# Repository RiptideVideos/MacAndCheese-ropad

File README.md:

# MacAndCheese-ropad

The MacAndCheese-ropad is a 4x4 macropad running on a Xiao RP2040. All 16 of the macropad buttons are fully customizable with the QMK firmware or other firmware that the RP2040 supports. 

The MacAndCheese-ropad is intended to be used for daily tasks like copying, pasting, taking a screenshot, ect. THe buttons can also be used as extra function buttons (up to 8 on MacOS and 12 on Windows). Using more adanced software, the buttons could be tied to app specific functions or really anything that can be run on a computer.

> Learn more about button use for QMK here: https://docs.qmk.fm/keycodes_basic

I built the MacAndCheese-ropad because I thought it would be a fun but not to hard challage, it has been just as expected. While some of it was smooth sailing a lot was feeling like I was in the dark on many things, however I was able to pull through and continue the project. I hope this macropad makes me more productive and proud to have somthing I worked hard on be usful to me.

## The Design:

The design features 16 square keys layed out in a 4x4 grid.
- The keys are Cherry MX switches.
- There is a empty space right of the keys which holds the Xiao RP2040.

> Onshape File: https://cad.onshape.com/documents/c366476147c6a16a111f20a0/w/74e1df7ada6eec6626497acf/e/e85a476c3b104135c352d93f?renderMode=0&uiState=69c80dd1942be0583aa661a2

## The PCB:

The PCB uses a matrix to support all 16 keys, a photo of the PCB in KiCad is below:

## The Firmware

The MacAndCheese-ropad uses the QMK firmware to give the keys uses, currentally the firmware is set up with 2 layers of keys. (The exact set up is in the repo).

## Bill of Materials

| Item | Qty | Source | Price | Unit Price | Provided by Hackpad? |
|------|-----|--------|-------|------------|----------------------|
| Seeed XIAO RP2040 | 1 | https://www.seeedstudio.com/XIAO-RP2040-v1-0-p-5026.html | $3.99 | $3.99 | Yes |
| 1N4148 Diodes | 16 | https://www.amazon.com/dp/B06XB1R2NK | ~$0.05	| $4.99 | Yes |
| Cherry MX Switches | 16 | https://www.amazon.com/Cherry-Switch-Mechanical-Keyboard-Switches/ | $0.55	| $19.99 | Yes |
| DSA Keycaps | 16 | https://www.amazon.com/Mechkeeb-Profile-Switches-Keyboard-Replacement/dp/B0BWDQ3NKK | ~$0.37 | $8.99 | Yes |
| PCB | 1 | JLC PCB | $4-7 | $4-7 | Via Grant |
| Soldering Iron | 1 | https://pine64.com/product/pinecil-smart-mini-portable-soldering-iron/ | $25.99 | $25.99 | Via Grant |

> Notes on BOM:
> The PCB price changes based on color, settings and deliver option.
> The exact Soldering Iron isn't needed for this project and you could get others online.

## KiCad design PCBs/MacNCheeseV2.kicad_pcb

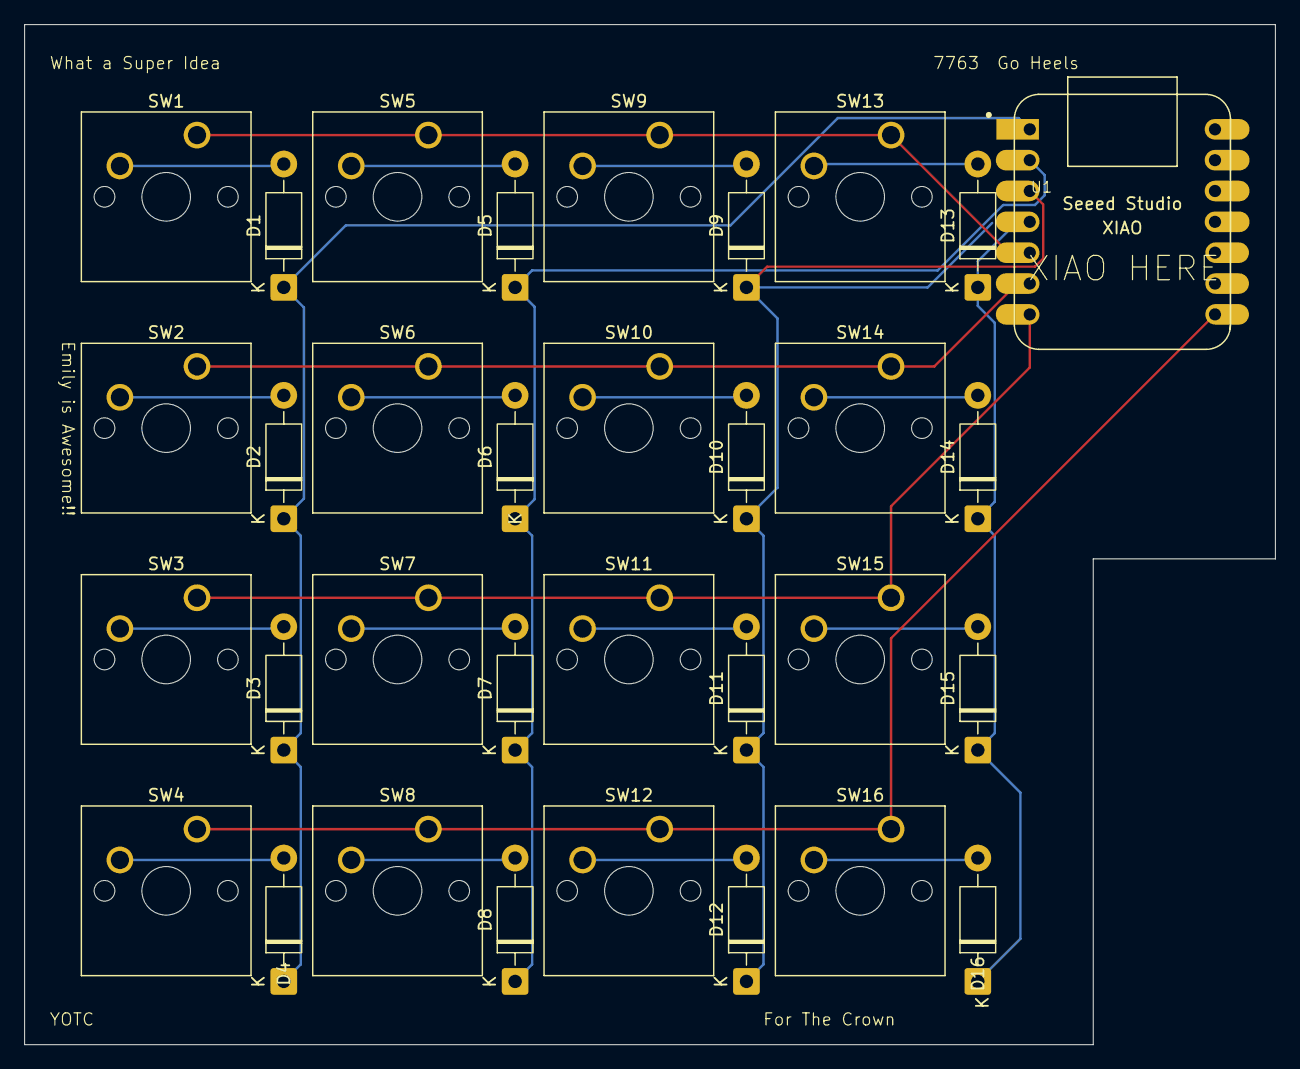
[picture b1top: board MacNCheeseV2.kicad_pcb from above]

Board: 2 copper layers, 103.0 x 84.0 mm, 33 parts (0 on the bottom side), 24 nets.

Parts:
D1, D2, D3, D4, D5, D6, D7, D8, D9, D10, D11, D12, D13, D14, D15, D16: 1N5819; D_DO-41_SOD81_P10.16mm_Horizontal
SW1, SW2, SW3, SW4, SW5, SW6, SW7, SW8, SW9, SW10, SW11, SW12, SW13, SW14, SW15, SW16: SW_Push; SW_Cherry_MX_1.00u_PCB
U1: MOUDLE-SEEEDUINO-XIAO; XIAO-Generic-Hybrid-14P-2.54-21X17.8MM

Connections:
/COL0: SW1.1, SW5.1, SW9.1, SW13.1, U1.5 (PA8_A4_D4_SDA)
/COL1: SW2.1, SW6.1, SW10.1, SW14.1, U1.6 (PA9_A5_D5_SCL)
/COL2: SW3.1, SW7.1, SW11.1, SW15.1, U1.7 (PB08_A6_D6_TX)
/COL3: SW4.1, SW8.1, SW12.1, SW16.1, U1.8 (PB09_A7_D7_RX)
/ROW0: D1.1 (K), D2.1 (K), D3.1 (K), D4.1 (K), U1.1 (PA02_A0_D0)
/ROW1: D5.1 (K), D6.1 (K), D7.1 (K), D8.1 (K), U1.2 (PA4_A1_D1)
/ROW2: D9.1 (K), D10.1 (K), D11.1 (K), D12.1 (K), U1.3 (PA10_A2_D2)
/ROW3: D13.1 (K), D14.1 (K), D15.1 (K), D16.1 (K), U1.4 (PA11_A3_D3)
unnamed: D1.2 (A), SW1.2
unnamed: D2.2 (A), SW2.2
unnamed: D3.2 (A), SW3.2
unnamed: D4.2 (A), SW4.2
unnamed: D5.2 (A), SW5.2
unnamed: D6.2 (A), SW6.2
unnamed: D7.2 (A), SW7.2
unnamed: D8.2 (A), SW8.2
unnamed: D9.2 (A), SW9.2
unnamed: D10.2 (A), SW10.2
unnamed: D11.2 (A), SW11.2
unnamed: D12.2 (A), SW12.2
unnamed: D13.2 (A), SW13.2
unnamed: D14.2 (A), SW14.2
unnamed: D15.2 (A), SW15.2
unnamed: D16.2 (A), SW16.2

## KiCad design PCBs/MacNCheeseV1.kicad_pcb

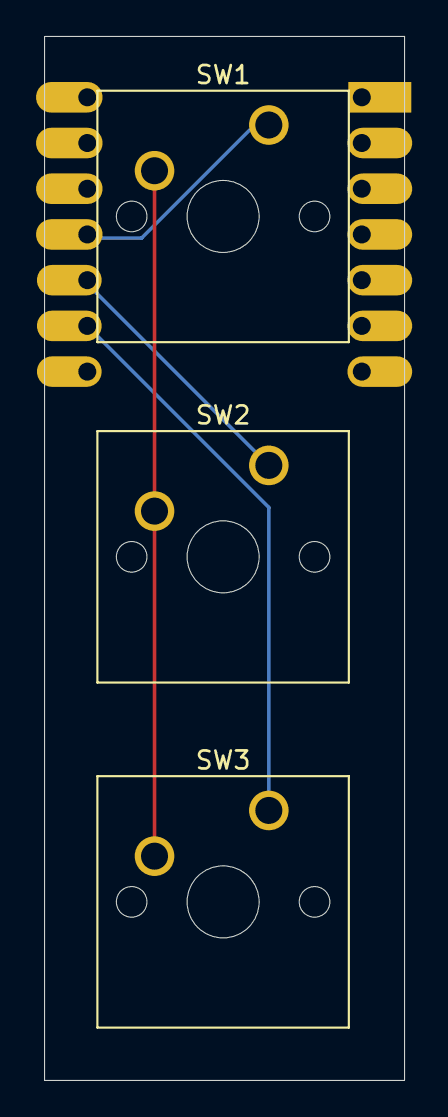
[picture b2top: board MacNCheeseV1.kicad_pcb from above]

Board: 2 copper layers, 20.0 x 58.0 mm, 4 parts (1 on the bottom side), 4 nets.

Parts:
SW1, SW2, SW3: SW_Push; SW_Cherry_MX_1.00u_PCB
U1: MOUDLE-SEEEDUINO-XIAO; XIAO-Generic-Hybrid-14P-2.54-21X17.8MM

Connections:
GND: SW1.2, SW2.2, SW3.2, U1.13 (GND)
unnamed: SW2.1, U1.10 (PA5_A9_D9_MISO)
unnamed: SW1.1, U1.11 (PA6_A10_D10_MOSI)
unnamed: SW3.1, U1.9 (PA7_A8_D8_SCK)

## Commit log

2026-03-06 PCB V1
    Basic design from the guide
2026-03-06 Create tobegone
2026-03-06 PCB V1
2026-03-11 Create a
2026-03-11 Test of 3x1 Design
2026-03-14 Create q
2026-03-14 Firmware for macropad
2026-03-15 MacNCheeseV2
2026-03-15 PCBs V2.1
    Added Designs
2026-03-20 PCB V2.2
    Slight design changes to make in <100mm
2026-03-20 4x4 V1 STEP
2026-03-20 Gerbers
2026-03-20 Create i
